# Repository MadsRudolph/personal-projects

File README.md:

# Personal DIY Projects

A collection of hardware projects focusing on audio, electronics, and 3D printing. Built and documented using Obsidian.

## 🎯 Active Projects

### 🧰 [Component Inventory Pro](components-inventory/)

Desktop app for cataloging THT electronic components with a built-in DTU shop browser. Track your parts, visualize resistor color bands, browse 1,400+ shop items, and see what you already own.

**Status:** 🟢 Working

**Key Features:**
- **Dashboard** with donut chart and stats
- **Inventory** with search, category filter, and visual resistor color bands
- **DTU Shop Browser** — browse/search/filter shop components, ownership cross-referencing
- **AI Export** — markdown summary for LLM-assisted project planning
- **Windows exe** — standalone build via PyInstaller

**Tech:** Python 3, customtkinter, SQLite, Pillow

---

### 🔊 [Illuminate 7Mk2 - 3D-Printed Speaker Build](Projects/Illuminate%207Mk2/Illuminate%207Mk2%20-%20Speaker%20Build.md)

Building a pair of audiophile-grade 3D-printed bookshelf speakers from scratch.

**Status:** 🟡 Planning

**Key Specs:**
- **Drivers:** Dayton Audio RS180P-8 (7" woofer) + RST28F-4 (28mm tweeter)
- **Enclosure:** 3D-printed PLA (~4750g required)
- **Frequency Response:** 50Hz - 20kHz (-3dB)
- **Impedance:** 8Ω nominal
- **Amplifier:** Fosi Audio V3 (TPA3255-based Class D, 300W x 2 @ 4Ω)

**Budget:** ~1750-2730 DKK (~$250-390 USD)

**Documentation:**
- [📋 Parts List](Projects/Illuminate%207Mk2/Parts%20List%20-%20Illuminate%207Mk2.md) - Complete BOM with suppliers and prices
- [📖 Build Log](Projects/Illuminate%207Mk2/Build%20Log%20-%20Illuminate%207Mk2.md) - Detailed build progress tracker
- [⚡ Amplifier Details](Projects/Illuminate%207Mk2/Amplifier%20-%20Fosi%20Audio%20V3.md) - Fosi Audio V3 specifications and setup

**Resources:**
- [Parts & Purchase Guide PDF](Resources/Illuminate%207Mk2/Illuminate_7_Mk2_Parts_and_Purchase_Guide.pdf)
- [Spec Sheet PDF](Resources/Illuminate%207Mk2/Illuminate_7Mk2_Spec_Sheet.pdf)

---

### ⚡ [Pi Zero 2W PWM Audio Filter](Projects/Pi%20Zero%20PWM%20Filter/Pi%20Zero%202W%20PWM%20Audio%20Filter.md)

Filtered PWM audio output for Raspberry Pi Zero 2W running Raspotify (Spotify Connect).

**Status:** 🟢 Working Prototype

**Key Specs:**
- **Platform:** Raspberry Pi Zero 2W
- **Software:** Raspotify (Spotify Connect)
- **Filter:** 3rd order Sallen-Key (RC + active, TL072)
- **Output:** Stereo line-level via screw terminals
- **PWM Attenuation:** -40.6dB @ 31.25kHz
- **Optimal Volume:** ALSA PCM at 75% (-22.6 dB)

**Tested With:**
- Active speakers (direct connection) — clean audio
- Schiit Saga preamp — working, noise floor at high gain

**Documentation:**
- [📋 Main Project](Projects/Pi%20Zero%20PWM%20Filter/Pi%20Zero%202W%20PWM%20Audio%20Filter.md) - Filter designs, BOM, Pi configuration
- [🔧 Build Guide](Projects/Pi%20Zero%20PWM%20Filter/Build%20Guide%20-%203rd%20Order%20PWM%20Filter.md) - Step-by-step build with AD3 testing

---

### 📡 [ESP32 IR Blaster - Smart Home IR Controller](Projects/ESP32%20IR%20Blaster/ESP32%20IR%20Blaster%20-%20Smart%20Home.md)

WiFi-connected IR blaster/receiver using ESP32 and ESPHome, integrating with Home Assistant to control any IR device.

**Status:** 🟢 Proof of Concept Complete

**Key Specs:**
- **Platform:** ESP32 with ESPHome firmware
- **Integration:** Home Assistant (native API)
- **IR Transmitter:** SFH4546 LED via 2N2222 driver
- **IR Receiver:** VS1838 (38 kHz demodulator)
- **Protocols:** NEC (including repeat codes for hold buttons)

**HAOS Add-on:** [IR Remote Wizard](https://github.com/MadsRudolph/ir-remote-wizard) — Auto-discovery add-on using the Flipper-IRDB database to find IR codes for your devices without manual learning.

**Documentation:**
- [📋 Main Project](Projects/ESP32%20IR%20Blaster/ESP32%20IR%20Blaster%20-%20Smart%20Home.md) - Circuit design, BOM, ESPHome config
- [🔧 Learning Remote Codes](Projects/ESP32%20IR%20Blaster/Learning%20Remote%20Codes%20-%20ESP32%20IR%20Blaster.md) - How to capture and add IR codes

---

### 💳 [RFID Card Reader - Bare Metal AVR](Projects/RFID%20Card%20Reader/RFID%20Card%20Reader.md)

Bare-metal RFID card reader using MFRC522 and Arduino Uno. Reads 13.56 MHz MIFARE card UIDs over serial. Pure embedded C with direct ATmega328P register access — no Arduino framework.

**Status:** 🟡 Proof of Concept

**Key Specs:**
- **MCU:** ATmega328P (Arduino Uno), bare-metal C
- **RFID Module:** MFRC522 RC522 (13.56 MHz, ISO 14443A)
- **Interface:** Hardware SPI (~1 MHz)
- **Output:** UART serial at 9600 baud
- **Build System:** PlatformIO (atmelavr, no framework)

**Documentation:**
- [📋 Main Project](Projects/RFID%20Card%20Reader/RFID%20Card%20Reader.md) - Wiring, software architecture, technical notes

---

### 🔬 [DTU Digital Multimeter](Projects/DTU%20Multimeter/DTU%20Multimeter%20-%20Digital%20Multimeter.md)

Fluke 289-class auto-ranging digital multimeter — bare-metal AVR C firmware on ATmega2560.

**Status:** 🟡 In Development

**Key Specs:**
- **MCU:** ATmega2560 @ 16 MHz (Arduino Mega 2560)
- **ADC:** MCP3208 12-bit SPI (100 ksps) + 64x oversampling
- **Display:** SSD1306 128x64 OLED (I2C)
- **Modes:** 22 measurement modes (DC/AC V, R, I, C, L, freq, temp, scope...)
- **Build System:** PlatformIO, pure avr-gcc (no Arduino framework)

**Documentation:**
- [📋 Main Project](Projects/DTU%20Multimeter/DTU%20Multimeter%20-%20Digital%20Multimeter.md) - Full specs, circuit design, component list
- [🔧 Build Guide](Projects/DTU%20Multimeter/Build%20Guide%20-%20DTU%20Multimeter.md) - Assembly, flashing, calibration

---

## 📂 Repository Structure

```
├── components-inventory/              # Component Inventory Pro app
│   ├── inventory_gui.py              # GUI (customtkinter)
│   ├── inventory.py                  # Data layer & CLI
│   ├── dist/InventoryPro.exe         # Windows executable
│   └── test_browser_data.py          # Tests
├── Projects/
│   ├── Illuminate 7Mk2/              # Speaker build project
│   ├── Pi Zero PWM Filter/           # PWM audio filter project
│   ├── ESP32 IR Blaster/             # Smart home IR controller
│   ├── RFID Card Reader/            # Bare-metal RFID reader
│   └── DTU Multimeter/              # Digital multimeter project
├── Resources/
│   ├── Illuminate 7Mk2/              # Speaker resources
│   └── Pi Zero PWM Filter/           # PWM filter resources
├── ir-remote-wizard/                  # HAOS add-on (git submodule)
├── Notes/                            # Quick reference notes
└── Home.md                           # Vault index
```

---

## 🛠️ Tech Stack

- **Documentation:** Obsidian (markdown-based)
- **Desktop Apps:** Python 3, customtkinter, SQLite, Pillow, PyInstaller
- **3D Modeling/Printing:** PLA filament, support-free design
- **Electronics:** Analog filters, crossover networks, IR circuits, bare-metal AVR firmware
- **Audio:** Dayton Audio drivers, Fosi Audio amplification, PWM filtering
- **Smart Home:** Home Assistant, ESPHome, ESP32
- **Embedded:** Raspberry Pi Zero 2W, ESP32, ATmega328P, ATmega2560, avr-gcc, PlatformIO
- **Version Control:** Git + GitHub

---

## 🎓 Background

I'm a Diplomingeniør (B.Eng.) student at DTU studying Electrical Engineering with focus on:
- Analog & mixed-signal electronics
- Electroacoustics & transducers
- Power electronics (Class D amplifiers, SMPS)
- Digital signal processing

These projects combine my academic knowledge with hands-on building experience.

---

## 🏷️ Topics

`audio` `speakers` `diy` `3d-printing` `electroacoustics` `electronics` `amplifiers` `class-d` `power-electronics` `raspberry-pi` `spotify` `esp32` `esphome` `home-assistant` `smart-home` `ir-remote` `rfid` `avr` `bare-metal` `embedded` `atmega2560` `multimeter` `obsidian` `python` `customtkinter` `sqlite` `inventory`

---

## 📊 Project Backlog

Future projects I'm considering:

### Audio
- [ ] Headphone amplifier build
- [ ] DAC project with AK4493 or ES9038Q2M
- [ ] Subwoofer design
- [ ] Room acoustic treatment

### Electronics
- [ ] ESP32-based audio streamer
- [ ] PCB design practice (audio circuits)
- [ ] Custom power supply builds

### 3D Printing
- [ ] 3D printer upgrades
- [ ] Custom equipment enclosures
- [ ] Functional prints for workshop organization

---

## 🔗 Links

- **GitHub:** [@MadsRudolph](https://github.com/MadsRudolph)
- **PrintYourSpeakers:** [printyourspeakers.com](https://www.printyourspeakers.com)
- **Dayton Audio:** [parts-express.com](https://www.parts-express.com)
- **Fosi Audio:** [fosiaudio.com](https://fosiaudio.com)

---

## 📝 Notes

This repository uses Obsidian for project documentation. To view with full functionality:
1. Install [Obsidian](https://obsidian.md)
2. Clone this repository
3. Open the folder as an Obsidian vault

Alternatively, all files are standard markdown and can be viewed directly on GitHub.

---

**Last Updated:** 2026-03-03

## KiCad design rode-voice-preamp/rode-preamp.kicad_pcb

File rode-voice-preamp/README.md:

# RØDE VideoMic GO preamp board

A milled PCB for the mic preamp in the RØDE voice satellite (`~/Projects/rode-voice`). It
replaces the breadboard. The VideoMic GO runs on plug-in power from the Uno's 3V3, an LM358
amplifies by ×564 (55 dB) in two AC-coupled stages, and the output goes to the Uno's A0 through
an RC filter.

- Single-sided, 63 x 41 mm. All copper is on the bottom (B.Cu) and the parts go on top.
- The GND pour connects to its pads solid, with no thermal spokes.
- CNC rule: 1.0 mm track, 0.85 mm clearance, for the 0.8 mm flat end mill. The 2.54 mm header's
  own pads are 0.84 mm apart, which `rode-preamp.kicad_dru` allows for J2 only.
- Checks run on this board:
  - Schematic: `sch_score` passes all 13 checks, ERC has 0 errors (3 `lib_symbol_mismatch`
    warnings on the LM358, which are harmless), and the netlist was read back and checked node
    by node.
  - Board: 13/13 nets connected, 0 vias, 0 wire bridges, and the GND pour is one piece. DRC
    shows 0 violations and 0 unconnected items, with 0 schematic parity issues. One soft
    ground-quality metric is marginal: C3's return runs a little far round the pour (1.07
    board diagonals against a 1.0 guideline).
- ngspice, LM358 as a 1 MHz single-pole model: bias 1.80 V on every stage, 55 dB at 1 kHz,
  −3 dB at 16 Hz and 4.4 kHz. The top corner sits below the 7 kHz you'd expect from the
  220p/470p caps because the LM358's bandwidth at ×100 adds a third pole. That is still plenty
  for speech.

## Connectors

| | Pin | Signal |
|---|---|---|
| J1 (screw terminal, left edge) | 1 | MIC: tip and ring of the mic cable, twisted together |
| | 2 | GND: sleeve |
| J2 (header, top right) | 1 | Uno 3V3 |
| | 2 | Uno 5V |
| | 3 | Uno A0 |
| | 4 | Uno GND |

J2's order is 3V3, 5V, A0, GND on purpose. 5V and A0 leave neighbouring LM358 pins (8 and 7),
so they sit next to each other on the header too and GND stays outside them. That is what lets
the board route on one layer with no wire bridges. The pins are labelled on the silkscreen.

## Bill of materials

`rode-preamp_bom.csv` is in the format that Parts Bin's Projects → Import BOM reads.

| Ref | Part | From |
|---|---|---|
| R1 | 2.2 k | home |
| R2, R3, R6 | 100 k | shop `100K` |
| R4 | 56.2 k | shop `56K2` |
| R5, R9 | 1.01 k | home |
| R7 | 10 k | home |
| R8 | 46.4 k | home |
| C1, C2, C3, C5 | 10 µF 50 V electrolytic | home. Bend the leads from 2.0 to 2.5 mm; + is marked on the silk |
| C4 | 220 pF ceramic | shop `220p` |
| C6 | 470 pF ceramic | shop `470p` |
| C7 | 10 nF ceramic | shop `10n` |
| C8 | 100 nF ceramic | shop `100n` |
| U1 | LM358 | home, in a shop `DIP8 Socket` |
| J1 | 2-pole screw terminal, 5 mm | shop `2 pol skrueterminal` |
| J2 | 4-pin male header, 2.54 mm | shop `4-Pin Male` (Molex KK pins fit the 1.0 mm holes) |

R5, R8 and R9 are the values already in the drawer: 1.01 k, 46.4 k and 1.01 k instead of
1 k, 47 k and 1 k. That gives gains of ×100 and ×5.6, bias 1.80 V and an RC corner of 16 kHz.

## Making it

- **Mill:** `production/gerbers/` holds `B_Cu`, `Edge_Cuts` and the Excellon `.drl`. Isolate B.Cu
  with an 0.8 mm tool and let the CAM do the mirroring, so don't pre-mirror. The holes are
  0.8 mm (42), 1.0 mm (4, J2) and 1.3 mm (2, J1).
- **Laser silkscreen:** `production/rode-preamp_silk_top.dxf`, top side, not mirrored.
- `rode-preamp_bottom_cu.dxf` is the copper outline. It's useful as a visual check and isn't
  the mill's input.

## Files

| File | What |
|---|---|
| `rode-preamp.kicad_sch` | Schematic, the source of truth. `draw_schematic.py` regenerates it (close KiCad first) |
| `rode-preamp.kicad_pcb` | Placed and routed board |
| `rode-preamp.place.json` | The hand placement, as footprint anchor x, y and rotation |
| `production/` | Gerbers, drill file, silk DXF, schematic PDF, layout and 3D renders |

The placement was done by hand because the block placer's layouts left 4–7 nets unrouted. The
rails run along the top edge with 3V3 on the outer track. Stage A's feedback parts sit above the
LM358 and stage B's to its right, and OUT_A runs under the package between the pin rows.
FreeRouting routed that placement single-sided in one pass.

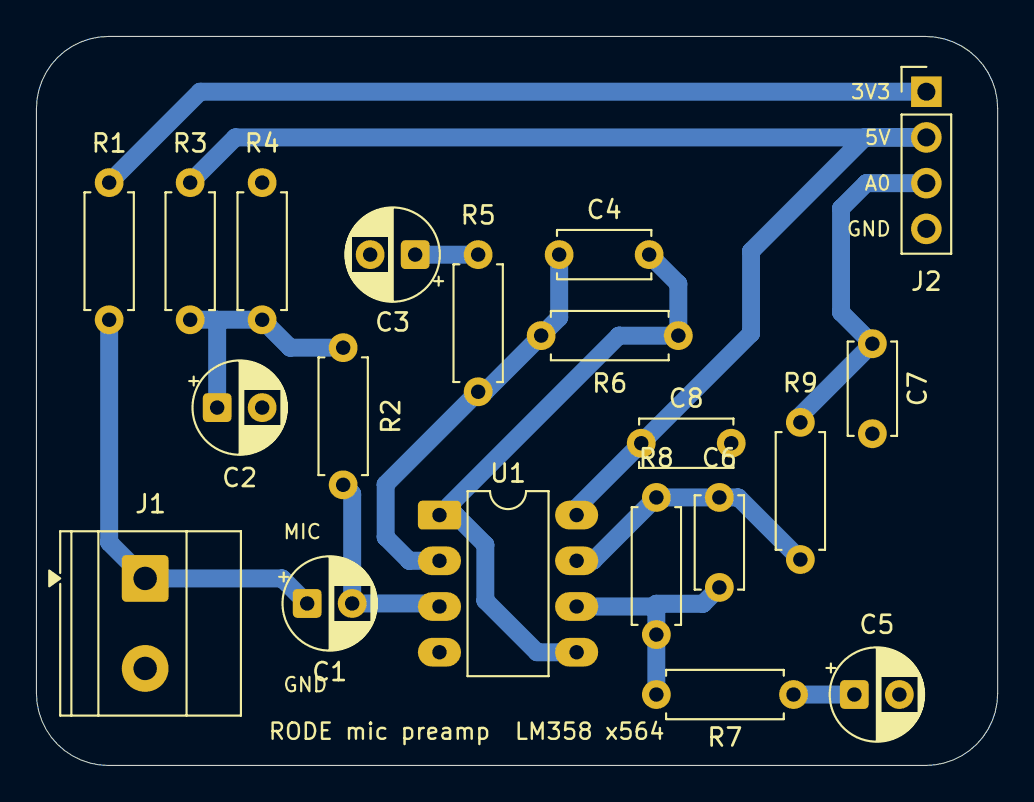
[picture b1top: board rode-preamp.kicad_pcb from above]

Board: 2 copper layers, 53.4 x 40.5 mm, 20 parts (0 on the bottom side), 13 nets.

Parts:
C1, C2, C3, C5: 10u; CP_Radial_D5.0mm_P2.50mm
C4: 220p; C_Disc_D5.0mm_W2.5mm_P5.00mm
C6: 470p; C_Disc_D5.0mm_W2.5mm_P5.00mm
C7: 10n; C_Disc_D5.0mm_W2.5mm_P5.00mm
C8: 100n; C_Disc_D5.0mm_W2.5mm_P5.00mm
J1: MIC IN; TerminalBlock_Phoenix_MKDS-1,5-2_1x02_P5.00mm_Horizontal
J2: TO UNO; PinHeader_1x04_P2.54mm_Vertical
R1: 2.2k; R_Axial_DIN0207_L6.3mm_D2.5mm_P7.62mm_Horizontal
R2, R3, R6: 100k; R_Axial_DIN0207_L6.3mm_D2.5mm_P7.62mm_Horizontal
R4: 56.2k; R_Axial_DIN0207_L6.3mm_D2.5mm_P7.62mm_Horizontal
R5, R9: 1.01k; R_Axial_DIN0207_L6.3mm_D2.5mm_P7.62mm_Horizontal
R7: 10k; R_Axial_DIN0207_L6.3mm_D2.5mm_P7.62mm_Horizontal
R8: 46.4k; R_Axial_DIN0207_L6.3mm_D2.5mm_P7.62mm_Horizontal
U1: LM358; DIP-8_W7.62mm_LongPads

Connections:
+3V3: J2.1, R1.1
+5V: C8.1, J2.2, R3.1, U1.8
/A0: C7.1, J2.3, R9.2
/BIAS: C2.1, R2.2, R3.2, R4.1
/MIC: C1.1, J1.1, R1.2
/OUT_A: C4.2, R6.2, U1.1, U1.5
/OUT_B: C6.2, R8.2, R9.1, U1.7
GND: C2.2, C3.2, C5.2, C7.2, C8.2, J1.2, J2.4, R4.2, U1.4
unnamed: C3.1, R5.1
unnamed: C5.1, R7.1
unnamed: C1.2, R2.1, U1.3
unnamed: C4.1, R5.2, R6.1, U1.2
unnamed: C6.1, R7.2, R8.1, U1.6

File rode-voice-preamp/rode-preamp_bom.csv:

Reference,Qty,Value,Footprint,Source,Shop CSV entry,Notes
R1,1,2.2k,R_Axial_DIN0207_P7.62mm,home,,plug-in power from 3V3
"R2,R3,R6",3,100k,R_Axial_DIN0207_P7.62mm,shop,100K,
R4,1,56.2k,R_Axial_DIN0207_P7.62mm,shop,56K2,bias divider: 1.80 V
"R5,R9",2,1.01k,R_Axial_DIN0207_P7.62mm,home,,
R7,1,10k,R_Axial_DIN0207_P7.62mm,home,,
R8,1,46.4k,R_Axial_DIN0207_P7.62mm,home,,stage B gain 5.6
"C1,C2,C3,C5",4,10u 50V electrolytic,CP_Radial_D5.0mm_P2.50mm,home,,bend leads from 2.0 to 2.5 mm; + marked on silk
C4,1,220p,C_Disc_D5.0mm_P5.00mm,shop,220p,
C6,1,470p,C_Disc_D5.0mm_P5.00mm,shop,470p,
C7,1,10n,C_Disc_D5.0mm_P5.00mm,shop,10n,
C8,1,100n,C_Disc_D5.0mm_P5.00mm,shop,100n,decoupling at U1 pin 8
U1,1,LM358,DIP-8_W7.62mm_LongPads,home,,
U1 socket,1,DIP-8 socket,(in U1 footprint),shop,DIP8 Socket,
J1,1,2-pole screw terminal 5 mm,TerminalBlock_Phoenix_MKDS-1.5-2_P5.00mm,shop,2 pol skrueterminal,mic cable: 1 MIC (tip+ring) / 2 GND (sleeve)
J2,1,4-pin male header 2.54 mm,PinHeader_1x04_P2.54mm,shop,4-Pin Male,1 3V3 / 2 5V / 3 A0 / 4 GND to the Uno

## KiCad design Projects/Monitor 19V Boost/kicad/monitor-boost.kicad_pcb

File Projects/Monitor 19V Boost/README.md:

# Monitor 19 V boost: 12 V → 19 V / 3 A for the Samsung C27JG5x

The C27JG5x runs from a 19 V / 2.53 A (48 W) adapter. On a 12 V supply it browns
out and shows artifacts. This board boosts a mains-powered 12 V supply to a
regulated 19 V. The 230 V side stays inside a certified 12 V supply. Everything
built here runs at 25 V or less.

Almost every part comes from the DTU component shop. Only the inductor wire, a
fuse, the barrel-plug lead and the 12 V supply come from elsewhere. The board is
single-sided and through-hole, isolation-milled on the CNC with a 0.8 mm end
mill.

| File | What it is |
|---|---|
| `calc/boost_design.py` → `boost_design.out` | all the design arithmetic: operating point, stresses, losses, divider, loop gain |
| `sim/boost_tran.cir` | ngspice switching transient of the whole circuit (behavioural SG3524) |
| `sim/run_corners.sh` → `corners.txt` | the same at Vin 11.4 / 12.0 / 12.6 V |
| `sim/boost_tran.png`, `sim/plot.py` | soft start, 1→3→1 A load steps |
| `kicad/monitor-boost.kicad_sch` / `.pdf` / `.png` | schematic (KiCad 10) |
| `kicad/tools/boost_layout.py` | the script that draws the schematic. Edit this, not the `.kicad_sch` |
| `kicad/lib/boost.kicad_sym` | SG3524 symbol (KiCad ships none) |
| `kicad/lib/energy_system.pretty` | mill footprints: narrowed TO-220/TO-126, 3 mm LED, toroid |
| `kicad/monitor-boost-bom.csv` | BOM with the exact shop CSV entry for every part |
| `kicad/monitor-boost.kicad_pcb`, `monitor-boost-pcb.png` | the routed single-sided board |
| `kicad/monitor-boost.kicad_dru` | the one DRC exception (pad-to-pad inside Q1..Q3, 0.84 mm) |
| `kicad/production/` | Gerbers + Excellon for the mill, silkscreen DXF for the laser |
| `kicad/tools/pcb_place.py` | builds and places the board (every part hand-placed, locked) |
| `kicad/tools/pcb_finish.py` | closes the links FreeRouting leaves, refills the pours |
| `kicad/tools/export_production.sh` | regenerates `production/` |
| `kicad/tools/kpy.py` | runs a script with pcbnew patched for Python 3.14 |

**Status:** schematic done and verified (netlist matches the target topology,
readability score PASS, ERC 0 errors, 2 benign `lib_symbol_mismatch` warnings),
simulated at three input corners, **board routed**: 88/88 connections, 0 vias,
0 clearance violations at the mill's 0.85 mm, one wire link. Footprints for the
electrolytics, 5 W shunts and the toroid are still the provisional ones -- check
them against the real parts before milling (see "Before milling").

## Why a boost and not a flyback

The shop cannot build an off-line flyback. Its highest-voltage MOSFET is
200 V (IRF640), and a flyback needs 600 V or more. It stocks no UC384x, TL431
or PC817, no bobbin and no magnet wire. A homemade single-sided board carrying
325 V DC would also be the riskiest item on the bench. A boost from a certified
12 V brick keeps every volt on this board below 25 V.

## Numbers

| | Vin 11.4 V | 12.0 V | 12.6 V |
|---|---|---|---|
| duty cycle | 0.45 | 0.42 | 0.39 |
| input / inductor current (3 A out) | 5.6 A | 5.3 A | 5.0 A |
| inductor peak | 6.7 A | 6.4 A | 6.1 A |
| **simulated** VOUT at 3 A | 19.08 V | 19.08 V | 19.08 V |
| **simulated** dip on a 1→3 A step | 18.26 V | 18.27 V | 18.29 V |
| **simulated** efficiency at 3 A | 91.4 % | 91.9 % | 92.3 % |

- **fsw 100 kHz.** R7 3.92 k, C12 3.3 nF, f = 1.30 / (RT·CT). Both SG3524
  outputs are paralleled, so the switch runs at the oscillator frequency with a
  maximum duty of about 90%.
- **L1 22 µH, Isat ≥ 9 A.** That stores 0.84 mJ at saturation. A powdered-iron
  core can hold that; an ungapped ferrite toroid cannot. See the inductor section.
- **Q1 STP36NF06** (60 V, 40 mΩ): Vds is 20 V plus ringing, and it dissipates
  about 1.1 W. It needs a small heatsink.
- **D1 BYW29-100** (8 A, 100 V ultrafast): it dissipates 2.6 W. **Heatsink
  required.** The shop has no power Schottky, so this diode is the biggest loss
  on the board.
- **Output:** 3 × 1000 µF / 50 V carry 2.7 A of ripple current in total. The
  simulated ripple is about 120 mV (0.6%).
- **VOUT** = 2.5 V × (1 + 205k/30.9k) = 19.06 V with RV1 centred. RV1 covers the
  SG3524's reference tolerance (4.6–5.4 V): with the reference at either limit,
  19 V is still reachable.
- **Soft start:** C13 sits on IN+, so the *reference* ramps up (τ 2.4 ms) and the
  loop tracks it. The simulation shows no overshoot (peak 19.03 V). My first
  version clamped COMP through a diode instead; it overshot 1 V because the
  error amp winds up.
- **Compensation:** voltage mode, type III around the SG3524's own error amp.
  Zeros are at 229 and 260 Hz (under the LC double pole at about 365 Hz); poles
  are at 9.2 kHz and 12 kHz. Crossover is about 0.7 kHz. Phase margin is at least
  67° and gain margin at least 15 dB across Vin 11.4–12.6 V, 1–3 A, and 30–150 mΩ
  ESR per output cap.
- **The SG3524 error amp is a 2 mS transconductance stage that sources only
  about 200 µA** (TI SLVS077). An output disturbance reaches IN− through R12, so
  the amp stays linear up to 200 µA × R12 ≈ 1 V. My first network used half
  these impedances and the simulated load step dipped 1.1 V; doubling them
  brought that to 0.8 V. Keep the network high-impedance.
- **Current limit:** R1‖R2 = 50 mΩ, R14/R15 halve the sense voltage, and CL+
  trips at 200 mV, which is 8 A peak. This protects Q1 only. **A boost cannot
  limit an output short** (the path runs 12 V → L1 → D1 → load), so fuse the
  12 V lead at 8 A slow-blow.
- **Over-voltage:** above about 23 V, D4 (BZX79C22) plus R16/R17 pull SHUTDOWN
  high. D2 (1.5KE24A) is the last clamp. The monitor never sees a runaway output
  even if the feedback divider opens.

What the simulation does **not** cover: SG3524 propagation delays, inductor
saturation, core loss, PCB parasitics and the error amp's 1.8 V common-mode
floor (IN+ passes below it briefly during soft start). Edge speeds and ringing
come from the bench, not from this model.

## The inductor

1. **Measure the core first.** Wind exactly 10 turns of any wire on the shop
   toroid and measure L with the AD3's impedance analyzer at 100 kHz. Then
   AL = L / 100 (nH per turn²).
   - AL of roughly 30–100 nH/N² means powdered iron: good.
   - AL above about 300 nH/N² means ungapped ferrite: **it will saturate at a few
     amps, so don't use it.** Try the other shop toroid, or buy a T106-26 or
     T130-26 (yellow/white).
2. **Turns** N = √(22000 / AL): 15 turns at AL 93, 19 turns at AL 60, 26 turns at
   AL 33.
3. **Wire:** 5.6 A RMS needs about 1.1 mm² of copper. Skin depth at 100 kHz is
   0.21 mm, so use 3 strands of 0.71 mm (or 2 × 0.9 mm) in parallel rather than
   one thick wire.
4. **Saturation test before it goes on the board:** 12 V from the bench supply
   with a big cap, the inductor, a logic-level IRL530 from the shop and a 0.1 Ω
   shunt. Drive the gate with a single 18 µs pulse from the AD3 wavegen (5 V is
   enough for the IRL530). The current should ramp in a straight line to about
   10 A. If it bends upward before 9 A, the core is saturating: add turns (L goes
   up as N², Isat drops only as 1/N), or use a bigger core.

## The board

148 x 118 mm, single-sided, through-hole, isolation-milled with the 0.8 mm end
mill (fits the 203 x 152 mm envelope). Every part is hand-placed and locked;
FreeRouting (`place_route.py`, planes-kept rung) routes everything except three
links, which `pcb_finish.py` closes.

**Ground is what drives the layout.** On a TO-220 the gate pin sits next to the
drain, so the gate line starts *inside* the input current loop (C_in -> L1 -> Q1
-> shunt -> GND -> C_in) and on one layer it has to cross that loop's ground
return somewhere. So:

- The input-loop return is a protected copper strip (a no-track keep-out, pour
  allowed) from C2's minus pad to the bottom of the shunts. Nothing crosses it
  in copper; **R4 (gate) and R6 (+12V -> VCC_F) straddle it** -- their bodies
  bridge it on the component side, their pads sit either side.
- The output loop's ground (C4..C6 minus -> shunt) is fenced off the same way,
  so VOUT sense goes round the outside to the feedback network.
- The switch node is a copper pour above the L1/Q1/D1 pad row, reaching into
  Q1's middle (drain) pad.
- Everything below the strip is the control section; its ground joins the power
  ground at the strip.

Two schematic changes came out of this and are in the sheet: R5 is gate-to-source
(it was gate-to-GND), and Q2 plus the SG3524 output collectors run from VCC_F
after R6 rather than raw +12 V (C9 supplies the gate-charge pulses).

**One wire link: CS, from R2's top pad to R14's bottom pad.** It is forced: CS
starts at the shunt inside the power section and CL+ is on U1's bottom row, walled
off by the gate-drive and VCC_F runs; both ends of U1 are taken (reference
divider, feedback network) and the space between U1's pin rows already carries
two tracks (the E_A/E_B join and IN-). CS is a 50 mOhm node, so a wire picks up
little and R14/C17 filter it at the pin. In the files it is an F.Cu track
(58 short segments, drawn clear of every pad); on the bench it is one insulated
wire, laid round the parts, soldered to those two pads.

**Rules:** track 1.0 mm (Default) / 1.5 mm (Power: +12V, GND, SW, VOUT, CS),
clearance 0.85 mm. The only DRC exception (`monitor-boost.kicad_dru`) is pad to
pad inside Q1..Q3 at 0.84 mm -- still wider than the tool. **Q2/Q3 use a TO-126
footprint with 2.54 mm pitch**: the stock 2.28 mm pitch leaves 0.58 mm between
pads, which the end mill cannot cut, so bend the BD139/BD140 legs out slightly.
DRC leaves only silkscreen overlaps (cosmetic, laser) and two single-spoke
thermals on signal ground pads (U1 pin 5, Q3 collector).

**Current capacity:** the power paths are pours or 1.5 mm tracks; the hot loop
(Q1 -> D1 -> C4..C6 -> ground -> shunt) is almost entirely pour.

### Before milling

- Measure the real diameter and lead pitch of the 1000 uF / 50 V caps and the
  0R10 5 W resistors, and the wound toroid. The footprints are placeholders
  (`CP_Radial_D16.0mm_P7.50mm`, `R_Axial_Power_L25.0mm_W9.0mm_P27.94mm`, the
  energy-system toroid). If one changes, edit `kicad/tools/pcb_place.py`, then
  place -> route -> finish -> export again:

  ```
  python3 kicad/tools/boost_layout.py
  python3 kicad/tools/pcb_place.py
  python3 kicad/tools/kpy.py ~/.claude/skills/kicad-place/scripts/place_route.py route kicad/monitor-boost.kicad_pcb --out /tmp/route
  python3 kicad/tools/kpy.py kicad/tools/pcb_finish.py /tmp/route/run1/Piso/monitor-boost.routed.kicad_pcb
  sh kicad/tools/export_production.sh
  ```
- Check the shop's trimmer against the 3296W pinout.
- Heatsinks: Q1 and D1 tabs are live (drain = SW, cathode = VOUT). Separate
  heatsinks, or one with the shop's mica pads and bushings.

**Tooling notes for this machine:** FreeRouting 1.9.0 never finishes if the board
already holds any pre-routed track (fixed or protected) -- that is why SW is a pour
and the leftovers are closed afterwards. `pcbnew.SaveBoard` rewrites the sibling
`.kicad_pro` with 0.2 mm defaults, silently disarming DRC; the scripts put the real
one back. Arch's pcbnew on Python 3.14 needs `kpy.py` (a missing SWIG iterator
alias), and `board.Remove()` segfaults it.

## Bring-up

1. **No U1, no L1:** power at 12 V from the bench supply limited to 0.2 A.
   Check +12V, and check VCC_F and all pins of the empty DIP socket against GND.
2. **U1 in, L1 still out:** check REF = 5 V, a 1–3.5 V sawtooth at CT (pin 7)
   at 100 kHz, and gate pulses on Q1. Set RV1 to mid-travel before powering up.
3. **L1 in, no load**, bench limit 1 A: VOUT should come up to about 19 V.
   Trim RV1 to 19.0 V.
4. **OVP test, monitor disconnected:** lift one end of R10 (the loop loses
   feedback and runs away). The output must stop at about 23 V and the TVS must
   stay cold. Refit R10.
5. **Load:** 4 × 100 Ω / 5 W in parallel (25 Ω, 0.76 A) first. Then use an
   electronic load, or the monitor itself, up to 2.5–3 A. Watch VOUT on the
   scope while switching the load: it should dip and recover in about 1 ms with
   no ringing afterwards. Optional: measure the loop with the AD3's network
   analyzer by injecting across a 10 Ω resistor between VOUT and R10/R12.
6. **Thermal:** run 30 min at full load. D1 and Q1 tabs should stay below about
   90 °C.
7. **Inrush:** plug the 12 V in with the supply off, then switch it on. At the
   instant of connection the output caps charge straight through L1 and D1. With
   a stiff source the simulation shows a 70 A spike; a real supply's current
   limit tames it. Don't hot-plug the board onto a live supply.

Sources: [TI SG3524 datasheet (SLVS077)](https://www.ti.com/lit/ds/symlink/sg3524.pdf).
The monitor's 19 V / 2.53 A rating comes from replacement-adapter listings for
the C27JG50, so check the label on your unit.

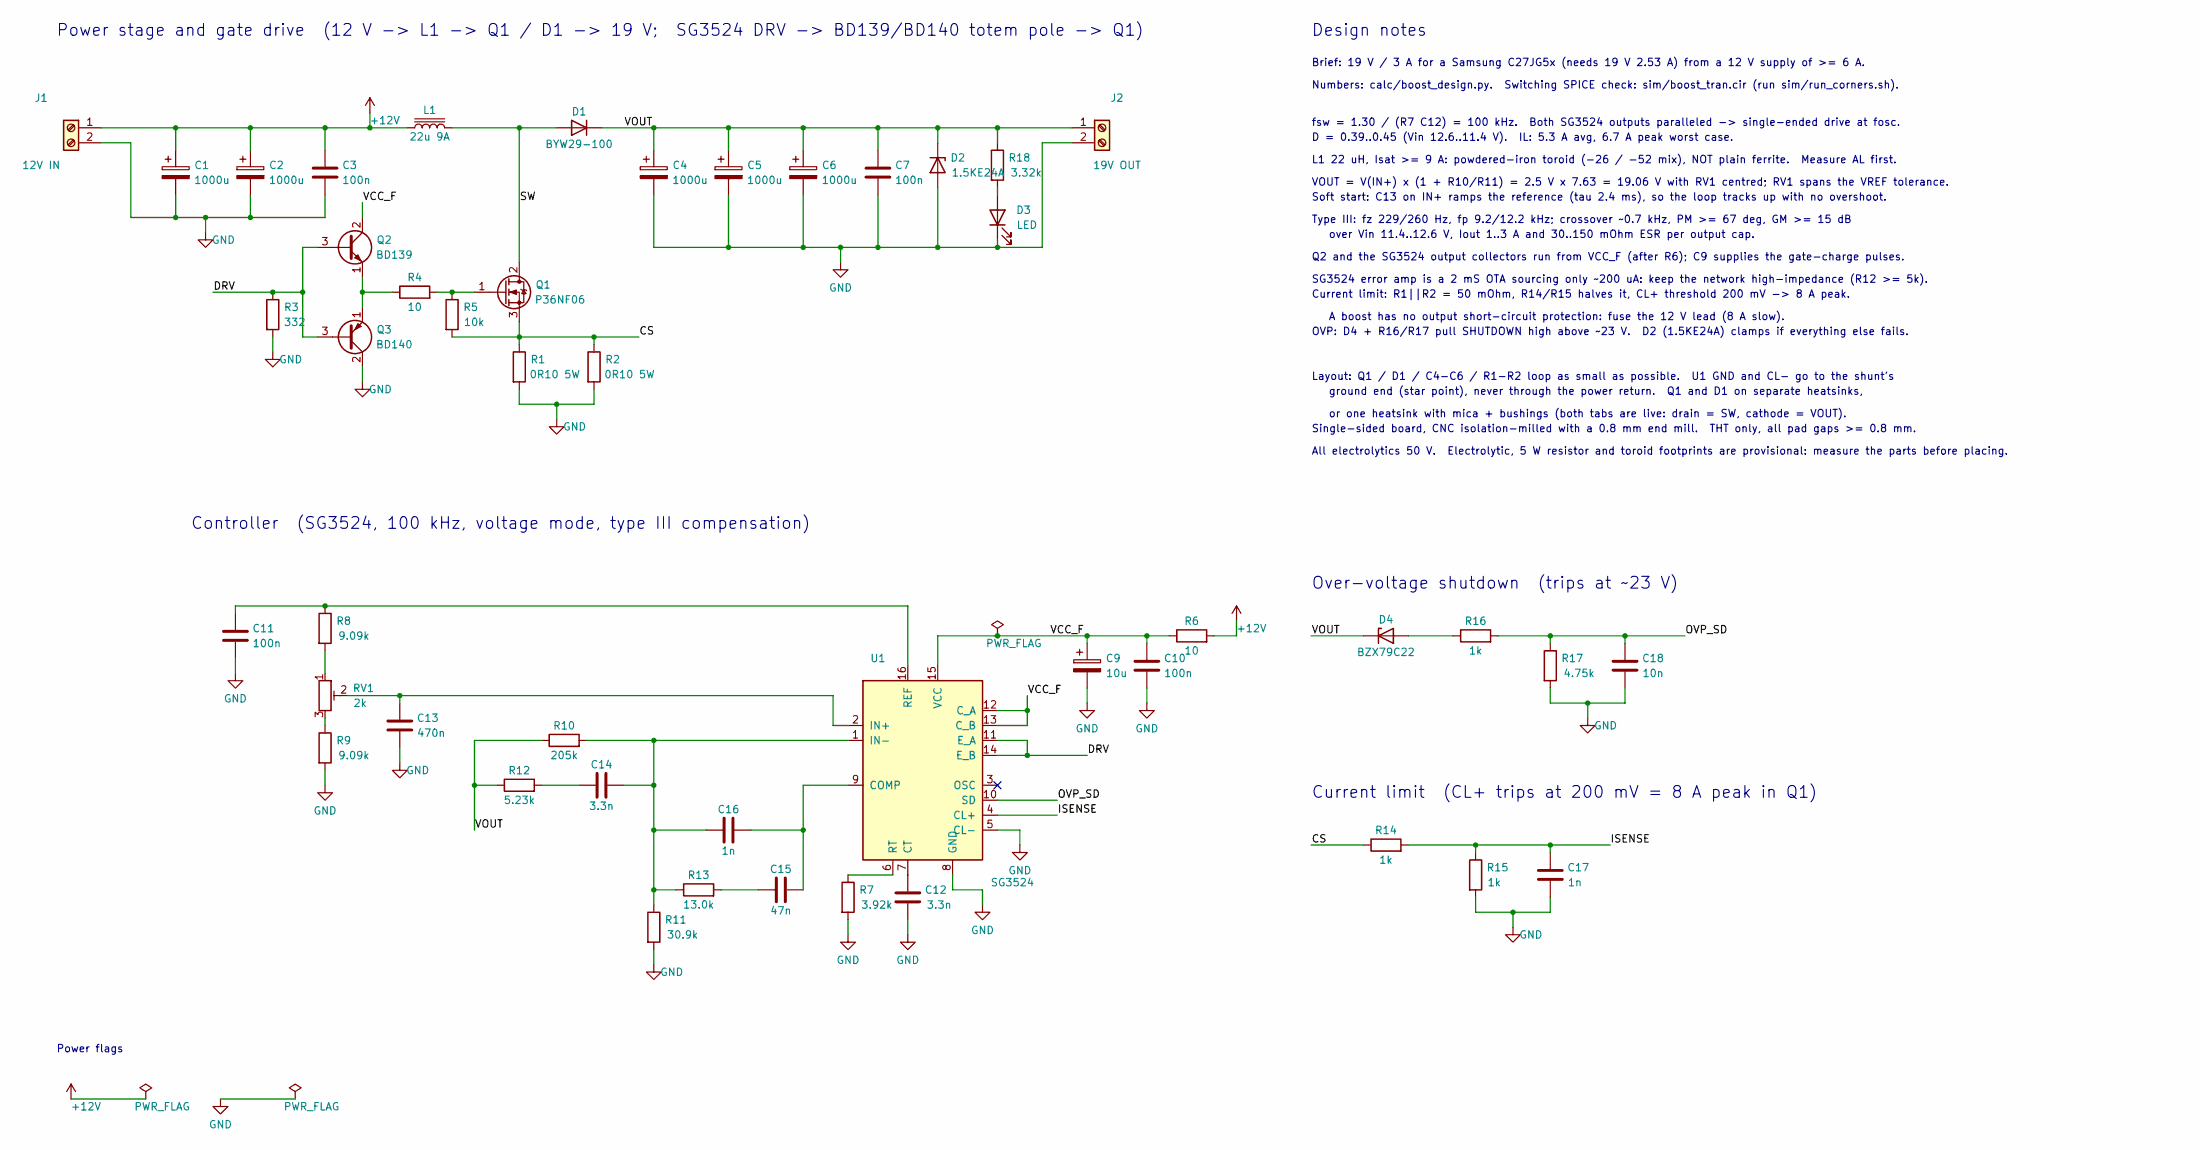
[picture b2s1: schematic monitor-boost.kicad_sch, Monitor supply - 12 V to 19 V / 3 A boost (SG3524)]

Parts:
C1, C2, C4, C5, C6: 1000u; CP_Radial_D16.0mm_P7.50mm
C3, C7, C10, C11: 100n; C_Disc_D5.0mm_W2.5mm_P5.00mm
C9: 10u; CP_Radial_D5.0mm_P2.50mm
C12, C14: 3.3n; C_Rect_L7.2mm_W3.0mm_P5.00mm_FKS2_FKP2_MKS2_MKP2
C13: 470n; C_Rect_L7.2mm_W5.5mm_P5.00mm_FKS2_FKP2_MKS2_MKP2
C15: 47n; C_Rect_L7.2mm_W3.0mm_P5.00mm_FKS2_FKP2_MKS2_MKP2
C16: 1n; C_Rect_L7.2mm_W3.0mm_P5.00mm_FKS2_FKP2_MKS2_MKP2
C17: 1n; C_Disc_D5.0mm_W2.5mm_P5.00mm
C18: 10n; C_Disc_D5.0mm_W2.5mm_P5.00mm
D1: BYW29-100; TO-220-2_Vertical
D2: 1.5KE24A; D_DO-201AE_P15.24mm_Horizontal
D3: LED; LED_D3.0mm_P5.08mm_LaserPads
D4: BZX79C22; D_DO-35_SOD27_P7.62mm_Horizontal
J1: 12V IN; TerminalBlock_MaiXu_MX126-5.0-02P_1x02_P5.00mm
J2: 19V OUT; TerminalBlock_MaiXu_MX126-5.0-02P_1x02_P5.00mm
L1: 22u 9A; L_Toroid_Vertical_L34.5mm_W15.0mm_P28.20mm_LaserPads
Q1: P36NF06; TO-220-3_Vertical_LaserPads
Q2: BD139; TO-126-3_Vertical_P2.54_LaserPads
Q3: BD140; TO-126-3_Vertical_P2.54_LaserPads
R1, R2: 0R10 5W; R_Axial_Power_L25.0mm_W9.0mm_P27.94mm
R3: 332; R_Axial_DIN0207_L6.3mm_D2.5mm_P10.16mm_Horizontal
R4, R6: 10; R_Axial_DIN0207_L6.3mm_D2.5mm_P10.16mm_Horizontal
R5: 10k; R_Axial_DIN0207_L6.3mm_D2.5mm_P10.16mm_Horizontal
R7: 3.92k; R_Axial_DIN0207_L6.3mm_D2.5mm_P10.16mm_Horizontal
R8, R9: 9.09k; R_Axial_DIN0207_L6.3mm_D2.5mm_P10.16mm_Horizontal
R10: 205k; R_Axial_DIN0207_L6.3mm_D2.5mm_P10.16mm_Horizontal
R11: 30.9k; R_Axial_DIN0207_L6.3mm_D2.5mm_P10.16mm_Horizontal
R12: 5.23k; R_Axial_DIN0207_L6.3mm_D2.5mm_P10.16mm_Horizontal
R13: 13.0k; R_Axial_DIN0207_L6.3mm_D2.5mm_P10.16mm_Horizontal
R14, R15, R16: 1k; R_Axial_DIN0207_L6.3mm_D2.5mm_P10.16mm_Horizontal
R17: 4.75k; R_Axial_DIN0207_L6.3mm_D2.5mm_P10.16mm_Horizontal
R18: 3.32k; R_Axial_DIN0207_L6.3mm_D2.5mm_P10.16mm_Horizontal
RV1: 2k; Potentiometer_Bourns_3296W_Vertical
U1: SG3524; DIP-16_W7.62mm_Socket_LongPads

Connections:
/CS: Q1.3 (S), R1.1, R2.1, R5.2, R14.1
/DRV: Q2.3 (B), Q3.3 (B), R3.1, U1.11 (E_A), U1.14 (E_B)
/ISENSE: C17.1, R14.2, R15.1, U1.4 (CL+)
/OVP_SD: C18.1, R16.2, R17.1, U1.10 (SD)
/SW: D1.2 (A), L1.2, Q1.2 (D)
/VOUT: C4.1, C5.1, C6.1, C7.1, D1.1 (K), D2.1 (K), D4.1 (K), J2.1, R10.1, R12.1, R18.1
unnamed: C14.1, R12.2
unnamed: C15.1, R13.2
unnamed: D3.2 (A), R18.2
unnamed: D4.2 (A), R16.1
unnamed: Q1.1 (G), R4.2, R5.1
unnamed: Q2.1 (E), Q3.1 (E), R4.1
unnamed: R8.2, RV1.1
unnamed: R9.1, RV1.3
unnamed: C15.2, C16.2, U1.9 (COMP)
unnamed: C12.1, U1.7 (CT)
unnamed: C13.1, RV1.2, U1.2 (IN+)
unnamed: C14.2, C16.1, R10.2, R11.1, R13.1, U1.1 (IN-)
unnamed: C11.1, R8.1, U1.16 (REF)
unnamed: R7.1, U1.6 (RT)

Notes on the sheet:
Power stage and gate drive (12 V -> L1 -> Q1 / D1 -> 19 V; SG3524 DRV -> BD139/BD140 totem pole -> Q1)
Controller (SG3524, 100 kHz, voltage mode, type III compensation)
Over-voltage shutdown (trips at ~23 V)
Current limit (CL+ trips at 200 mV = 8 A peak in Q1)
Power flags
Design notes
Brief: 19 V / 3 A for a Samsung C27JG5x (needs 19 V 2.53 A) from a 12 V supply of >= 6 A.
Numbers: calc/boost_design.py. Switching SPICE check: sim/boost_tran.cir (run sim/run_corners.sh).
fsw = 1.30 / (R7 C12) = 100 kHz. Both SG3524 outputs paralleled -> single-ended drive at fosc.
D = 0.39..0.45 (Vin 12.6..11.4 V). IL: 5.3 A avg, 6.7 A peak worst case.
L1 22 uH, Isat >= 9 A: powdered-iron toroid (-26 / -52 mix), NOT plain ferrite. Measure AL first.
VOUT = V(IN+) x (1 + R10/R11) = 2.5 V x 7.63 = 19.06 V with RV1 centred; RV1 spans the VREF tolerance.
Soft start: C13 on IN+ ramps the reference (tau 2.4 ms), so the loop tracks up with no overshoot.
Type III: fz 229/260 Hz, fp 9.2/12.2 kHz; crossover ~0.7 kHz, PM >= 67 deg, GM >= 15 dB
over Vin 11.4..12.6 V, Iout 1..3 A and 30..150 mOhm ESR per output cap.
Q2 and the SG3524 output collectors run from VCC_F (after R6); C9 supplies the gate-charge pulses.
SG3524 error amp is a 2 mS OTA sourcing only ~200 uA: keep the network high-impedance (R12 >= 5k).
Current limit: R1||R2 = 50 mOhm, R14/R15 halves it, CL+ threshold 200 mV -> 8 A peak.
A boost has no output short-circuit protection: fuse the 12 V lead (8 A slow).
OVP: D4 + R16/R17 pull SHUTDOWN high above ~23 V. D2 (1.5KE24A) clamps if everything else fails.
Layout: Q1 / D1 / C4-C6 / R1-R2 loop as small as possible. U1 GND and CL- go to the shunt's
ground end (star point), never through the power return. Q1 and D1 on separate heatsinks,
or one heatsink with mica + bushings (both tabs are live: drain = SW, cathode = VOUT).
Single-sided board, CNC isolation-milled with a 0.8 mm end mill. THT only, all pad gaps >= 0.8 mm.
All electrolytics 50 V. Electrolytic, 5 W resistor and toroid footprints are provisional: measure the parts before placing.

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
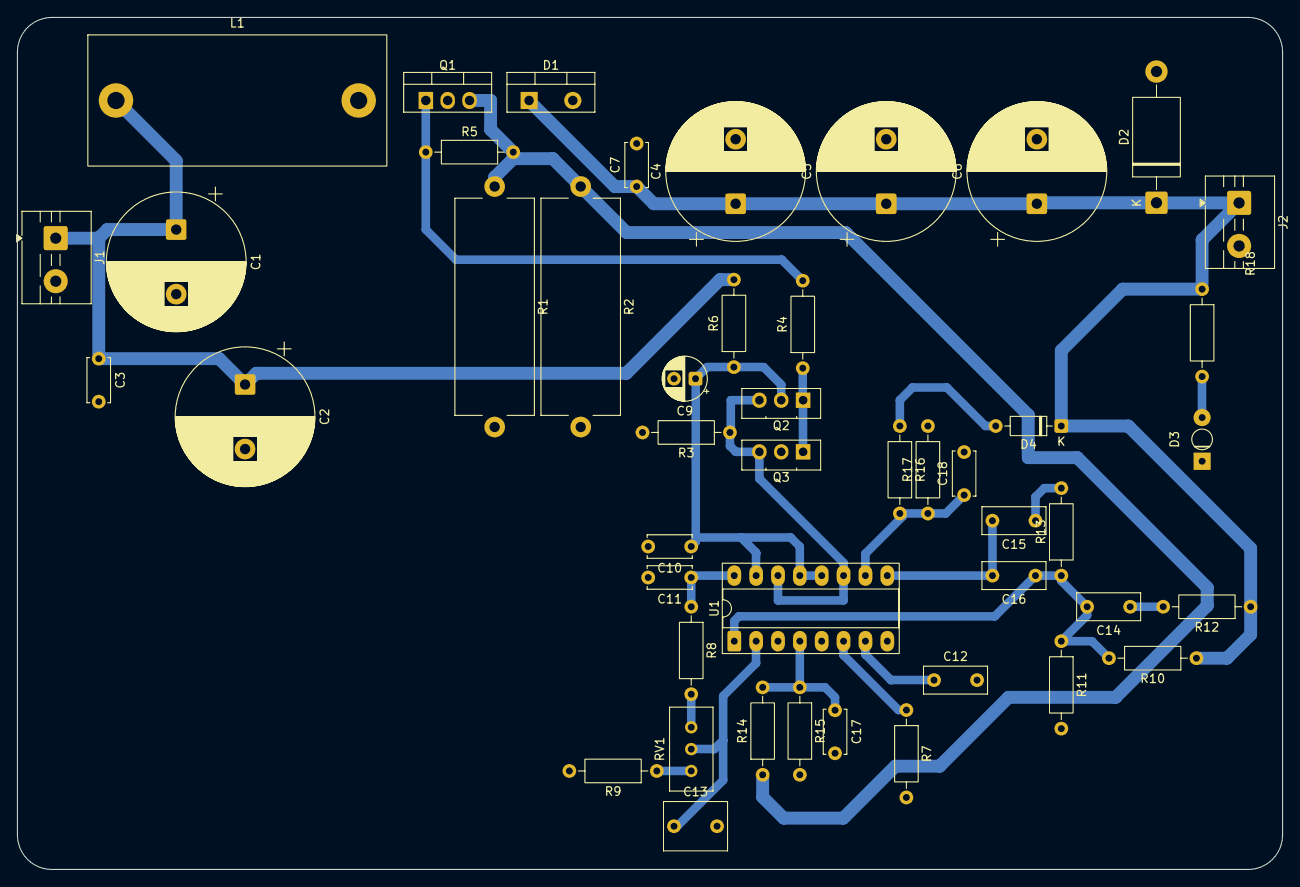
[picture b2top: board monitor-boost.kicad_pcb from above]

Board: 2 copper layers, 147.0 x 99.0 mm, 47 parts (0 on the bottom side), 23 nets.

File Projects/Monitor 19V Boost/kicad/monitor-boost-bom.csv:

Qty,Refs,Value,Shop CSV entry,Package / footprint,Role
1,U1,SG3524,"IC,Linear,SG3524",DIP-16 (socketed),PWM controller
1,-,DIP-16 socket,"Connector,IC Socket,DIP16 Socket",DIP-16,Socket for U1
1,Q1,STP36NF06,"Transistor,N-MOSFET,P36NF06",TO-220,Boost switch (IRF540 is the fallback)
1,Q2,BD139,"Transistor,NPN BJT,BD139",TO-126 (bend leads to 2.54 mm pitch),Totem-pole source
1,Q3,BD140,"Transistor,PNP BJT,BD140",TO-126 (bend leads to 2.54 mm pitch),Totem-pole sink
1,D1,BYW29-100,"Diode,Rectifier,BYW29",TO-220AC,Boost rectifier (8 A 100 V ultrafast)
1,D2,1.5KE24A,"Diode,TVS Zener,1.5KE24A",DO-201AE,Output TVS clamp
1,D3,LED 3 mm green,"LED,3mm,LED 3MM GRØN",3 mm,Output-on indicator
1,D4,BZX79C22,"Diode,Zener,BZX79C22",DO-35,OVP threshold
5,"C1,C2,C4,C5,C6",1000 uF 50 V,"Capacitor,Electrolytic,1000µF 50V",radial (measure D/pitch),Input (2) and output (3) bulk
1,C9,10 uF 50 V,"Capacitor,Electrolytic,10µF 50V",radial 5 mm / 2.5 mm,VCC filter
4,"C3,C7,C10,C11",100 nF,"Capacitor,Ceramic,100n",disc 5 mm pitch,HF bypass
1,C17,1 nF,"Capacitor,Ceramic,1n0",disc 5 mm pitch,Current-sense filter
1,C18,10 nF,"Capacitor,Ceramic,10n",disc 5 mm pitch,SHUTDOWN filter
2,"C12,C14",3.3 nF film,"Capacitor,Film,3n3",5 mm pitch,CT timing; type III C3
1,C13,470 nF film,"Capacitor,Film,470n",5 mm pitch,Soft start on IN+
1,C15,47 nF film,"Capacitor,Film,47n",5 mm pitch,Type III Cf
1,C16,1 nF film,"Capacitor,Film,1n0",5 mm pitch,Type III Cp
2,"R1,R2",0.10 Ohm 5 W,"Resistor,Power,0R10 5W",axial power (measure),Current shunt (50 mOhm total)
2,"R4,R6",10 Ohm,"Resistor,E96 Standard,10R0",0207,Gate resistor; VCC filter
1,R3,332 Ohm,"Resistor,E96 Standard,332R",0207,Emitter-output pull-down
3,"R14,R15,R16",1 kOhm,"Resistor,E96 Standard,1K00",0207,CS divider; OVP series
1,R18,3.32 kOhm,"Resistor,E96 Standard,3K32",0207,LED current
1,R7,3.92 kOhm,"Resistor,E96 Standard,3K92",0207,RT
1,R17,4.75 kOhm,"Resistor,E96 Standard,4K75",0207,OVP pull-down
1,R12,5.23 kOhm,"Resistor,E96 Standard,5K23",0207,Type III R3
2,"R8,R9",9.09 kOhm,"Resistor,E96 Standard,9K09",0207,VREF divider
1,R5,10 kOhm,"Resistor,E96 Standard,10K0",0207,Gate pull-down
1,R13,13.0 kOhm,"Resistor,E96 Standard,13K0",0207,Type III Rf
1,R11,30.9 kOhm,"Resistor,E96 Standard,30K9",0207,Feedback divider bottom
1,R10,205 kOhm,"Resistor,E96 Standard,205K",0207,Feedback divider top
1,RV1,2 kOhm trimmer,"Resistor,Trimmer,2K",3296W (check the shop part),Output voltage trim
2,"J1,J2",2-pole screw terminal,"Connector,Terminal,2 pol skrueterminal",5.0 mm pitch,12 V in / 19 V out
1,L1,toroid core,"Inductor,Toroid Core,Small Toroid (or Smaller Toroid)",off-board / vertical,22 uH -- measure AL first (README)
2,-,TO-220 heatsink,"Hardware,Heatsink,TO-220 Heatsink",-,One each for Q1 and D1
2,-,TO-220 mica + bushing,"Hardware,Thermal Pad,TO-220 Mica / Hardware,Mounting,TO-220 Isobøsning",-,Only if Q1 and D1 share a heatsink
,,,,,
,,NOT FROM THE SHOP,,,
1,L1,enamelled copper wire ~1.2 mm2 total,-,-,"e.g. 3 x 0.71 mm or 2 x 0.9 mm in parallel, ~1.5 m"
1,-,8 A slow fuse + holder,-,-,In the 12 V lead (a boost cannot limit an output short)
1,-,DC barrel plug + lead,-,-,Match the original Samsung adapter's plug (measure it)
1,-,12 V supply >= 6 A,-,-,Your parts-bin find; Mean Well LRS-100-12 if buying

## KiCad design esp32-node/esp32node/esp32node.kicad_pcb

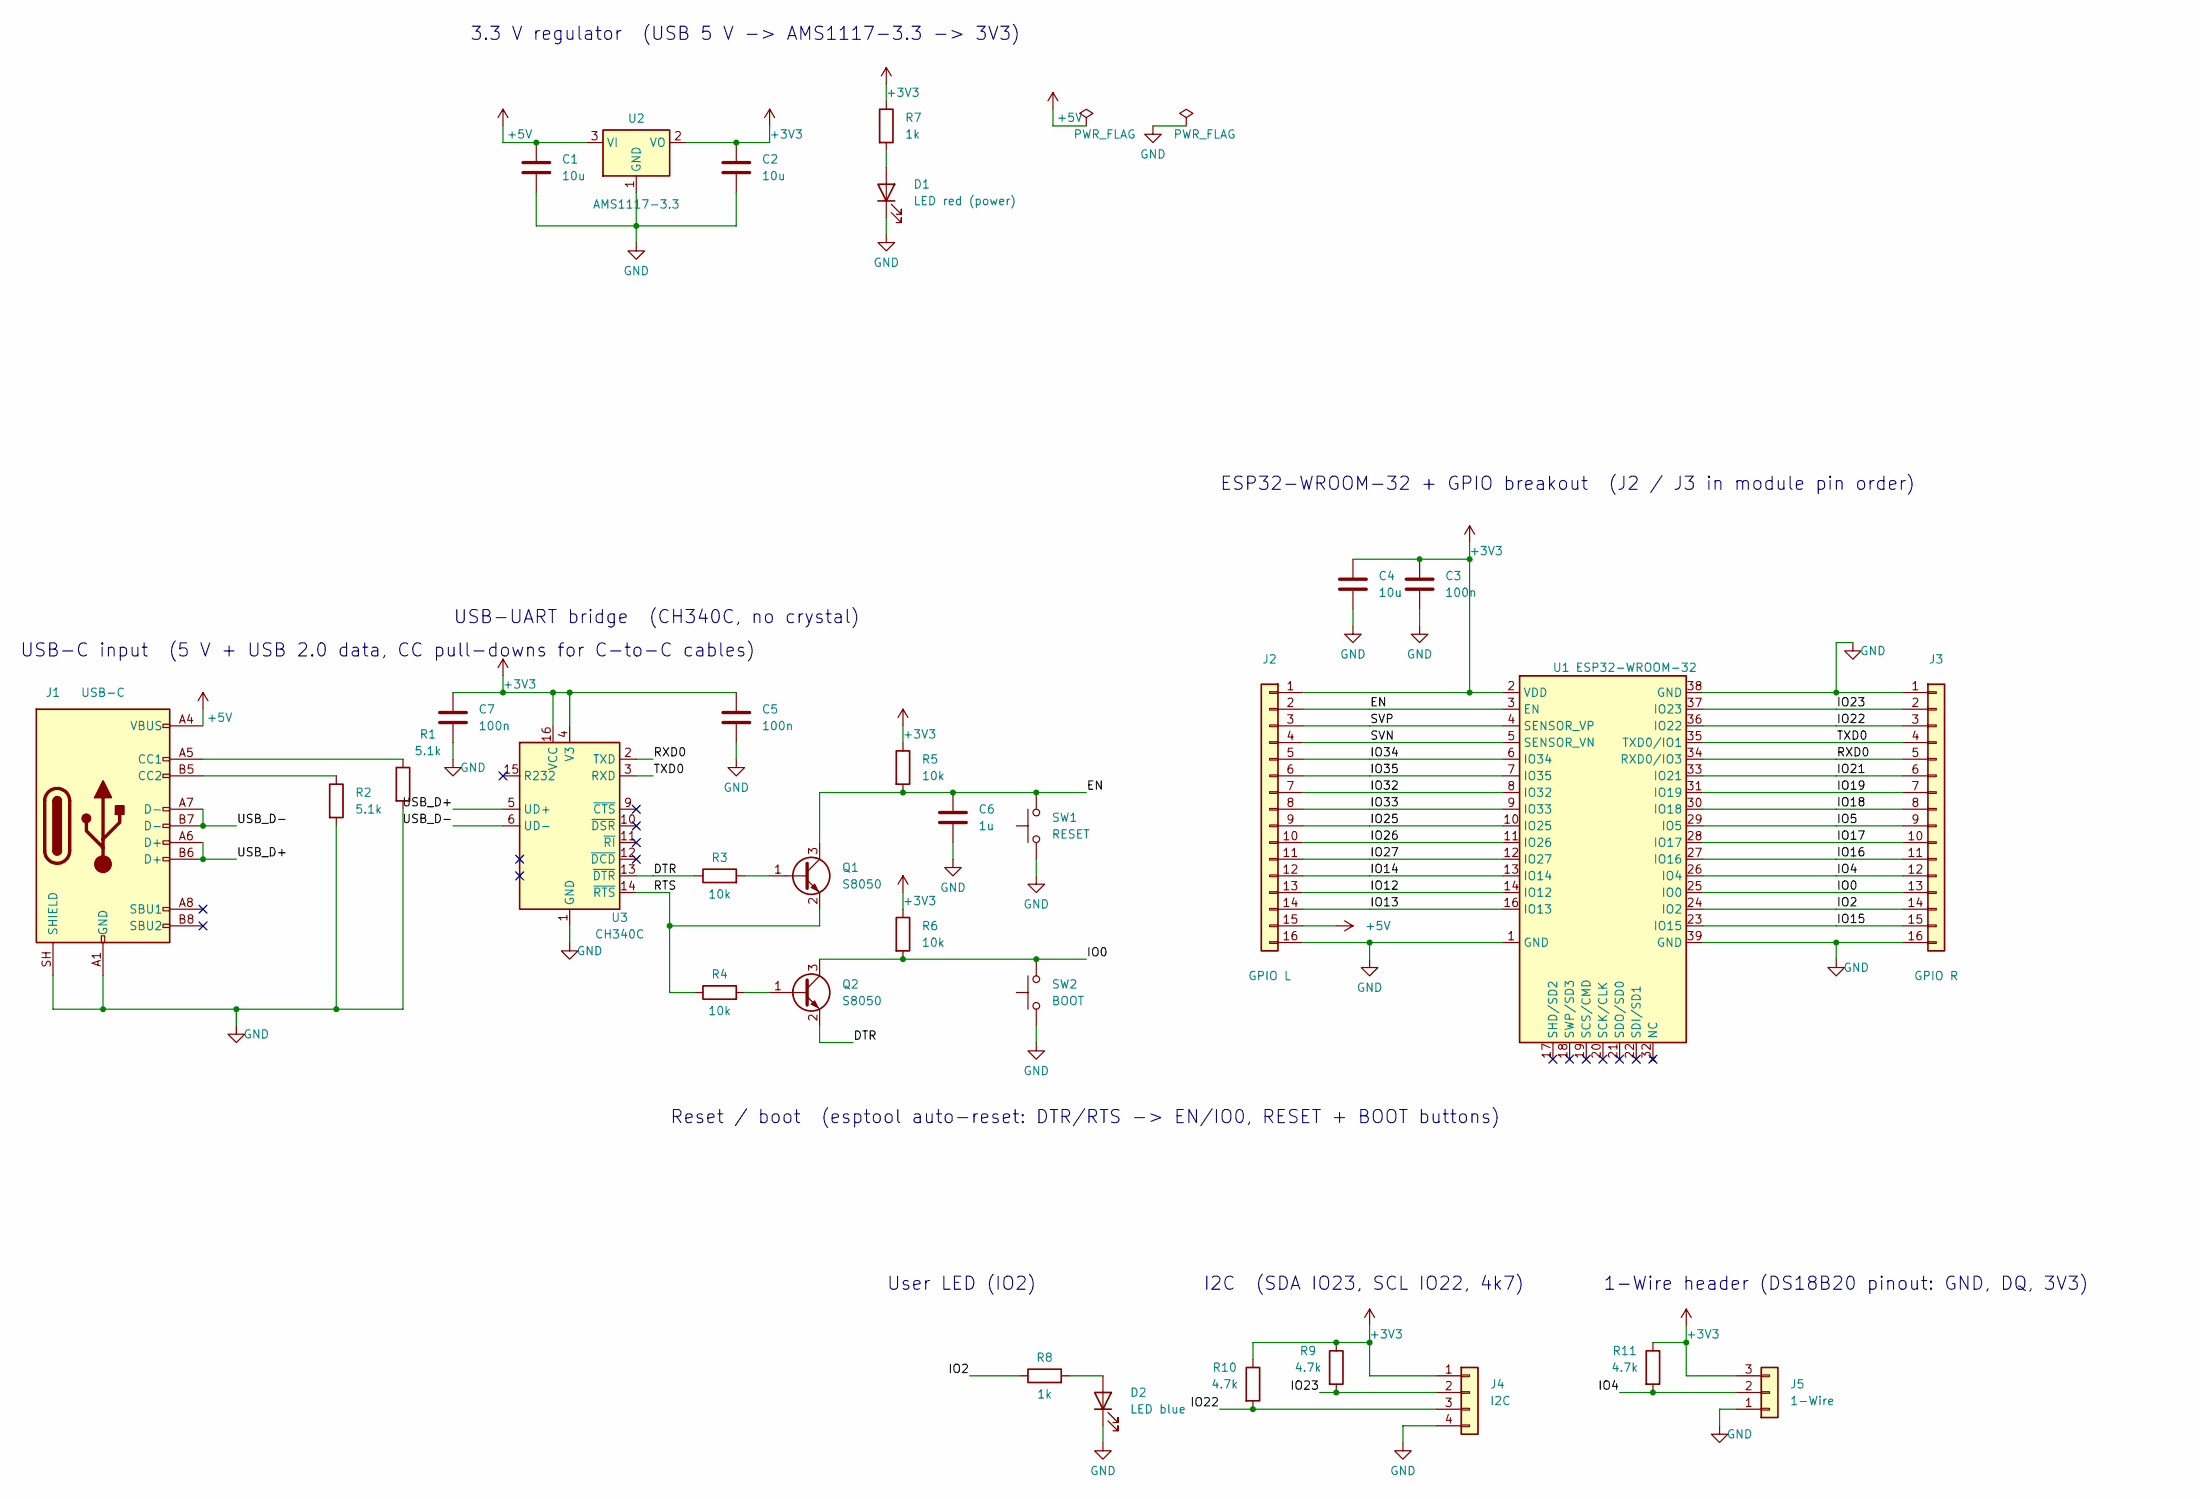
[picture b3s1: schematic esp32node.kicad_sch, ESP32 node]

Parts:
C1, C2, C4: 10u; C_0805_2012Metric
C3, C5, C7: 100n; C_0805_2012Metric
C6: 1u; C_0805_2012Metric
D1: LED red (power); LED_0805_2012Metric
D2: LED blue; LED_0805_2012Metric
J1: USB-C; USB_C_Receptacle_GCT_USB4105-xx-A_16P_TopMnt_Horizontal
J2: GPIO L; PinHeader_1x16_P2.54mm_Vertical
J3: GPIO R; PinHeader_1x16_P2.54mm_Vertical
J4: I2C; PinHeader_1x04_P2.54mm_Vertical
J5: 1-Wire; PinHeader_1x03_P2.54mm_Vertical
Q1, Q2: S8050; SOT-23
R1, R2: 5.1k; R_0805_2012Metric
R3, R4, R5, R6: 10k; R_0805_2012Metric
R7, R8: 1k; R_0805_2012Metric
R9, R10, R11: 4.7k; R_0805_2012Metric
SW1: RESET; SW_SPST_PTS645Sx43SMTR92
SW2: BOOT; SW_SPST_PTS645Sx43SMTR92
U1: ESP32-WROOM-32; ESP32-WROOM-32_NoVias
U2: AMS1117-3.3; SOT-223-3_TabPin2
U3: CH340C; SOIC-16_3.9x9.9mm_P1.27mm

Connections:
+3V3: C2.1, C3.1, C4.1, C5.1, C7.1, J2.1, J4.1, J5.3, R5.1, R6.1, R7.1, R9.1, R10.1, R11.1, U1.2 (VDD), U2.2 (VO), U3.4 (V3), U3.16 (VCC)
/DTR: Q2.2 (E), R3.1, U3.13 (~DTR)
/EN: C6.1, J2.2, Q1.3 (C), R5.2, SW1.2, U1.3 (EN)
/IO0: J3.13, Q2.3 (C), R6.2, SW2.2, U1.25 (IO0)
/IO2: J3.14, R8.1, U1.24 (IO2)
/IO4: J3.12, J5.2, R11.2, U1.26 (IO4)
/IO5: J3.9, U1.29 (IO5)
/IO12: J2.13, U1.14 (IO12)
/IO13: J2.14, U1.16 (IO13)
/IO14: J2.12, U1.13 (IO14)
/IO15: J3.15, U1.23 (IO15)
/IO16: J3.11, U1.27 (IO16)
/IO17: J3.10, U1.28 (IO17)
/IO18: J3.8, U1.30 (IO18)
/IO19: J3.7, U1.31 (IO19)
/IO21: J3.6, U1.33 (IO21)
/IO22: J3.3, J4.3, R10.2, U1.36 (IO22)
/IO23: J3.2, J4.2, R9.2, U1.37 (IO23)
/IO25: J2.9, U1.10 (IO25)
/IO26: J2.10, U1.11 (IO26)
/IO27: J2.11, U1.12 (IO27)
/IO32: J2.7, U1.8 (IO32)
/IO33: J2.8, U1.9 (IO33)
/IO34: J2.5, U1.6 (IO34)
/IO35: J2.6, U1.7 (IO35)
/RTS: Q1.2 (E), R4.1, U3.14 (~RTS)
/RXD0: J3.5, U1.34 (RXD0/IO3), U3.2 (TXD)
/SVN: J2.4, U1.5 (SENSOR_VN)
/SVP: J2.3, U1.4 (SENSOR_VP)
/TXD0: J3.4, U1.35 (TXD0/IO1), U3.3 (RXD)
/USB_D+: J1.A6 (D+), J1.B6 (D+), U3.5 (UD+)
/USB_D-: J1.A7 (D-), J1.B7 (D-), U3.6 (UD-)
unnamed: D1.2 (A), R7.2
unnamed: D2.2 (A), R8.2
unnamed: J1.A5 (CC1), R1.1
unnamed: J1.B5 (CC2), R2.1
unnamed: Q1.1 (B), R3.2
unnamed: Q2.1 (B), R4.2

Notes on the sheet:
3.3 V regulator (USB 5 V -> AMS1117-3.3 -> 3V3)
USB-C input (5 V + USB 2.0 data, CC pull-downs for C-to-C cables)
USB-UART bridge (CH340C, no crystal)
Reset / boot (esptool auto-reset: DTR/RTS -> EN/IO0, RESET + BOOT buttons)
ESP32-WROOM-32 + GPIO breakout (J2 / J3 in module pin order)
User LED (IO2)
I2C (SDA IO23, SCL IO22, 4k7)
1-Wire header (DS18B20 pinout: GND, DQ, 3V3)

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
